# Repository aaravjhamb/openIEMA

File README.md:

<h1 align="center">OpenIEMA</h1>
<div align="center">

**OpenIEMA** is an Open Source, In Ear Monitor Amplifier built as an alternative to the Behringer P2 with dual headphone outputs driven from a mono balanced XLR input, with onboard LiPo power and USB-C charging!!

</div>

## Key Features

| | |
|---|---|
| **True balanced input** | Neutrik XLR into an OPA1678 differential line receiver which ensures any long cable runs from the mixer stay noise free |
| **Dual 3.5mm outputs** | supports up to two IEM users off one beltpack, driven by a TI TPA6132A2 DirectPath amp! |
| **Analog soft limiter** | anti parallel LEDs act as soft limiters that clamp excess noise before you hear it! |
| **Fully portable** | Uses a 1S LiPo with USB C charging (MCP73831, 500 mA) and a boost converter to a clean 5 V analog rail, charges while switched off |
| **Zero firmware** | 100% analog signal path built for simplicity |
| **3D-printed enclosure** | Includes a 3D printed enclosure with volume control all in a compact package! |

## PCB

40 × 70 mm, 2-layer, designed in KiCad 10.

**Schematic:**

**Layout:**

**3D View:**

## Case

Designed in Fusion 360

## Credits

This project uses:

- [KiCad 10](https://www.kicad.org/) for schematic capture and layout
- [pcb2blender](https://github.com/30350n/pcb2blender) for the Blender renders
- TI TPA6132A2 + OPA1678, Microchip MCP73831, TI TPS61023

## License

MIT

---

> [aaravj.tech]() · GitHub [@aaravjhamb](https://github.com/aaravjhamb/)

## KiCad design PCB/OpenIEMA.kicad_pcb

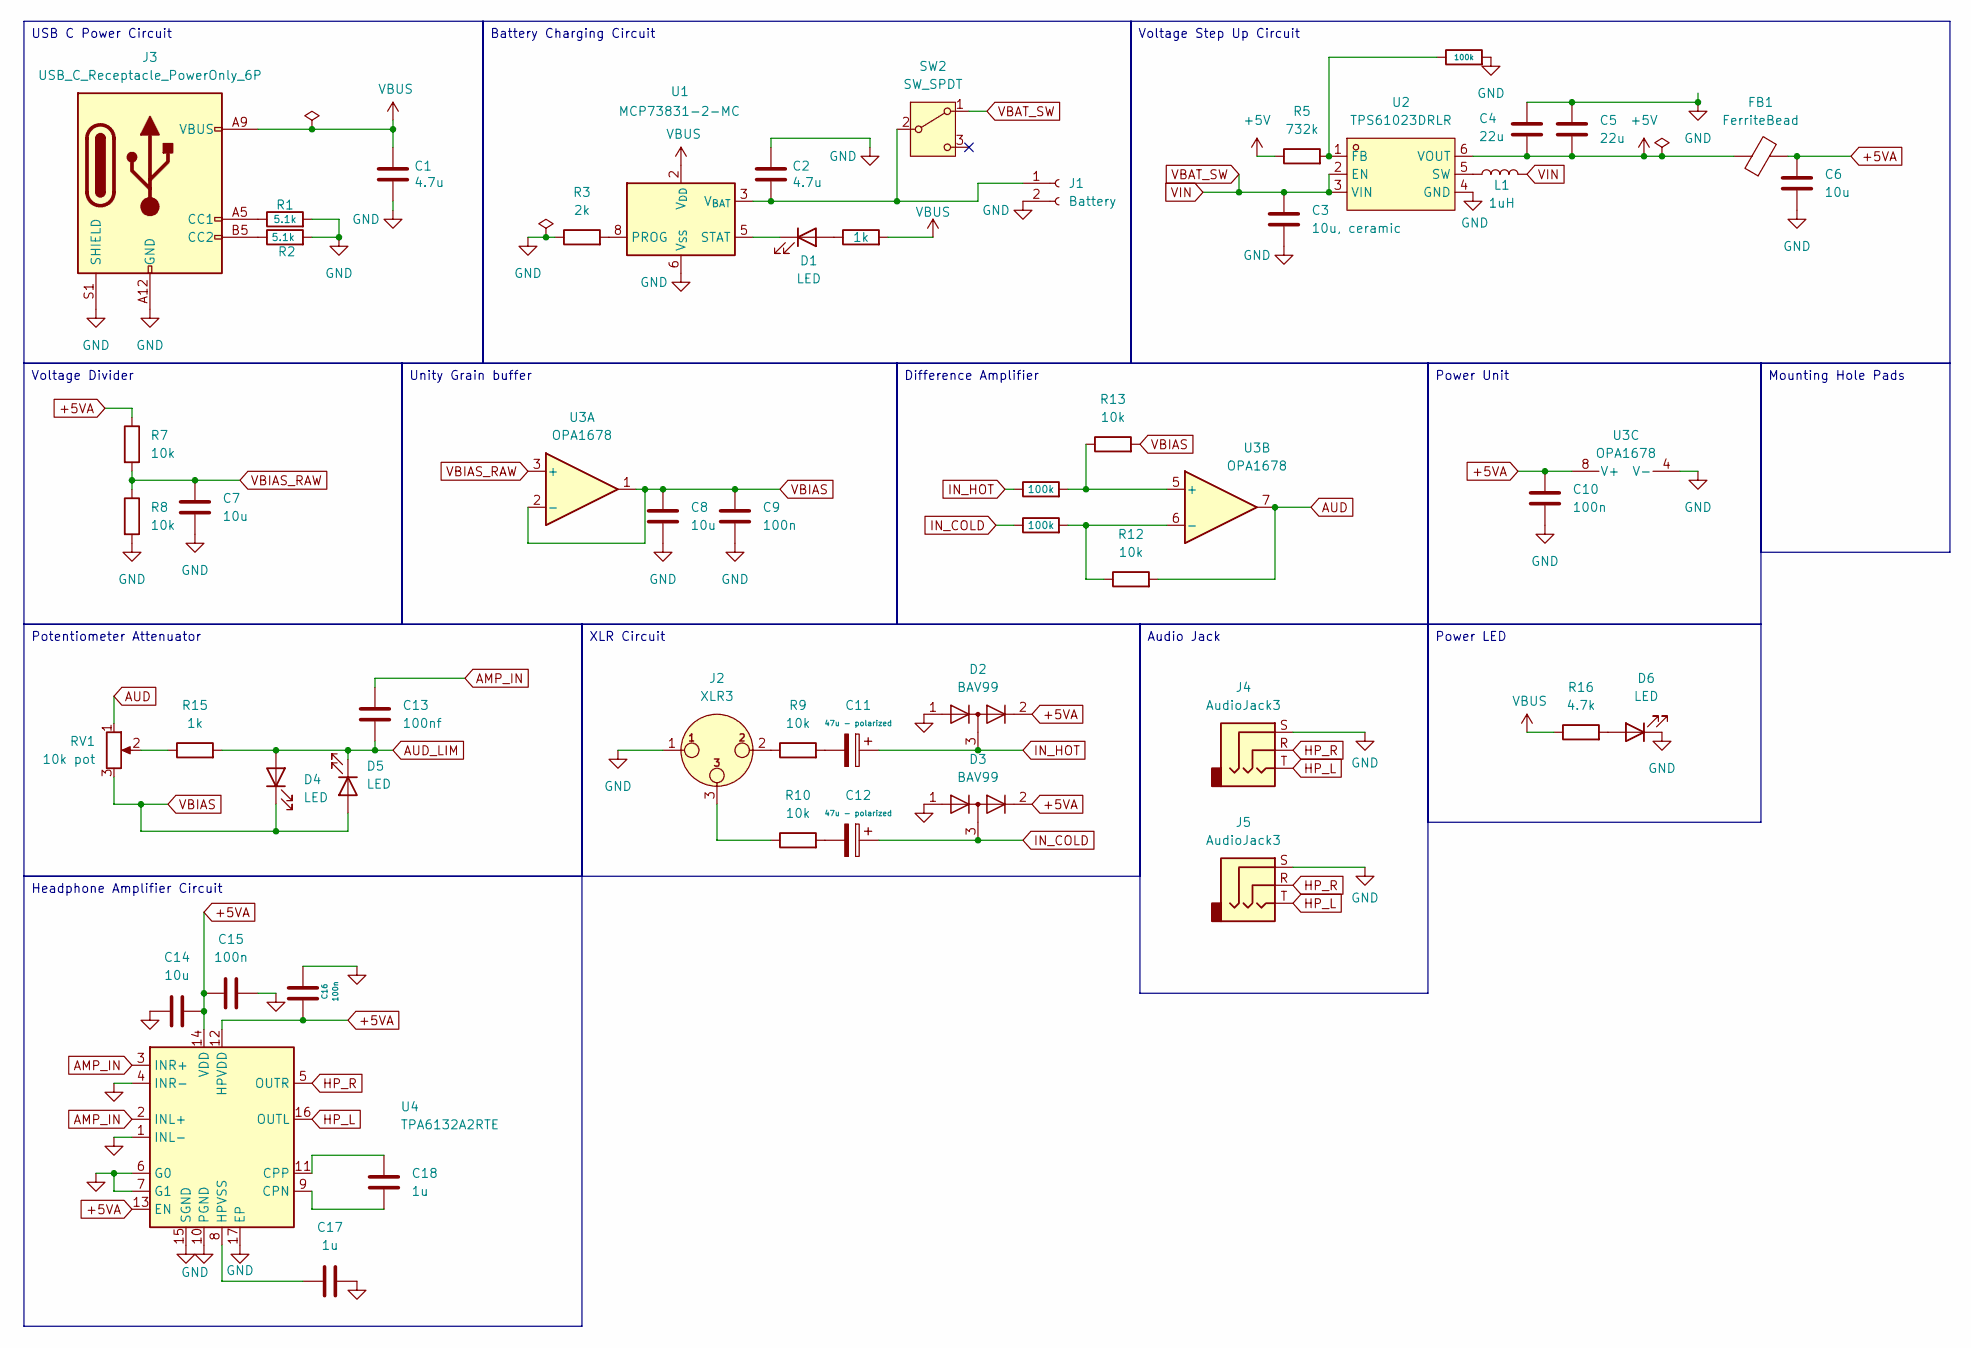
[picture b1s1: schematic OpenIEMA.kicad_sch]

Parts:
C1, C2: 4.7u; C_0402_1005Metric
C3: 10u, ceramic; C_0402_1005Metric
C4, C5: 22u; C_0402_1005Metric
C6, C7, C8, C14: 10u; C_0402_1005Metric
C9, C10, C15, C16: 100n; C_0402_1005Metric
C11, C12: 47u - polarized; CP_Elec_6.3x7.7
C13: 100nf; C_0402_1005Metric
C17, C18: 1u; C_0402_1005Metric
D1, D4, D5, D6: LED; LED_0402_1005Metric
D2, D3: BAV99; SOT-23
FB1: FerriteBead; R_0805_2012Metric
J1: Battery; JST_PH_B2B-PH-K_1x02_P2.00mm_Vertical
J2: XLR3; Jack_XLR_Neutrik_NC3FD-H_Horizontal
J3: USB_C_Receptacle_PowerOnly_6P; USB_C_Receptacle_HRO_TYPE-C-31-M-17
J4, J5: AudioJack3; Jack_3.5mm_PJ320A_Horizontal
L1: 1uH; L_Taiyo-Yuden_NR-40xx
R1, R2: 5.1k; R_0402_1005Metric
R3: 2k; R_0402_1005Metric
R4, R15: 1k; R_0402_1005Metric
R5: 732k; R_0402_1005Metric
R6, R11, R14: 100k; R_0402_1005Metric
R7, R8, R9, R10, R12, R13: 10k; R_0402_1005Metric
R16: 4.7k; R_0402_1005Metric
RV1: 10k pot; Potentiometer_Piher_PT-6-V_Vertical
SW2: SW_SPDT; SW_SPDT_PCM12
U1: MCP73831-2-MC; DFN-8-1EP_3x2mm_P0.5mm_EP1.7x1.4mm
U2: TPS61023DRLR; SOT-563_L1.6-W1.2-P0.50-LS1.6-BR; MPN TPS61023DRLR; LCSC Part C919459
U3: OPA1678; SOIC-8_3.9x4.9mm_P1.27mm
U4: TPA6132A2RTE; WQFN-16-1EP_3x3mm_P0.5mm_EP1.6x1.6mm_ThermalVias

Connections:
+5V: C4.2, C5.2, FB1.1, R5.1, U2.6 (VOUT)
+5VA: C6.1, C10.2, C14.2, C15.1, C16.1, D2.2 (A), D3.2 (A), FB1.2, R7.1, U3.8 (V+), U4.12 (HPVDD), U4.13 (EN), U4.14 (VDD)
AMP_IN: C13.1, U4.2 (INL+), U4.3 (INR+)
AUD: R12.2, RV1.1, U3.7
AUD_LIM: C13.2, D4.2 (A), D5.1 (K), R15.2
GND: C1.2, C2.1, C3.2, C4.1, C5.1, C6.2, C7.2, C8.1, C9.1, C10.1, C14.1, C15.2, C16.2, C17.1, D2.1 (K), D3.1 (K), D6.1 (K), J1.2, J2.1, J3.A12 (GND), J3.B12 (GND), J3.S1 (SHIELD), J4.S, J5.S, R1.2, R2.2, R3.1, R6.2, R8.2, U1.6 (V_{SS}), U2.4 (GND), U3.4 (V-), U4.1 (INL-), U4.4 (INR-), U4.6 (G0), U4.7 (G1), U4.10 (PGND), U4.15 (SGND), U4.17 (EP)
HP_L: J4.T, J5.T, U4.16 (OUTL)
HP_R: J4.R, J5.R, U4.5 (OUTR)
IN_COLD: C12.1, D3.3 (K), R11.1
IN_HOT: C11.1, D2.3 (K), R14.1
unnamed: C11.2, R9.2
unnamed: C12.2, R10.2
unnamed: D1.2 (A), R4.1
unnamed: D1.1 (K), U1.5 (STAT)
unnamed: D6.2 (A), R16.2
unnamed: C2.2, J1.1, SW2.2 (B), U1.3 (V_{BAT}), U1.4 (V_{BAT})
unnamed: J2.2, R9.1
unnamed: J2.3, R10.1
unnamed: J3.A5 (CC1), R1.1
unnamed: J3.B5 (CC2), R2.1
unnamed: R15.1, RV1.2
unnamed: R3.2, U1.8 (PROG)
unnamed: R5.2, R6.1, U2.1 (FB)
unnamed: L1.1, U2.5 (SW)
unnamed: R13.1, R14.2, U3.5 (+)
unnamed: R11.2, R12.1, U3.6 (-)
unnamed: C18.2, U4.9 (CPN)
unnamed: C18.1, U4.11 (CPP)
unnamed: C17.2, U4.8 (HPVSS)
VBAT_SW: C3.1, L1.2, SW2.1 (A), U2.2 (EN), U2.3 (VIN)
VBIAS: C8.2, C9.2, D4.1 (K), D5.2 (A), R13.2, RV1.3, U3.1, U3.2 (-)
VBIAS_RAW: C7.1, R7.2, R8.1, U3.3 (+)
VBUS: C1.1, J3.A9 (VBUS), J3.B9 (VBUS), R4.2, R16.1, U1.1 (V_{DD}), U1.2 (V_{DD})

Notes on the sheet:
Potentiometer Attenuator
Mounting Hole Pads
Voltage Step Up Circuit
Voltage Divider
Battery Charging Circuit
Audio Jack
Headphone Amplifier Circuit
Power LED
USB C Power Circuit
Power Unit
Difference Amplifier
Unity Grain buffer
XLR Circuit

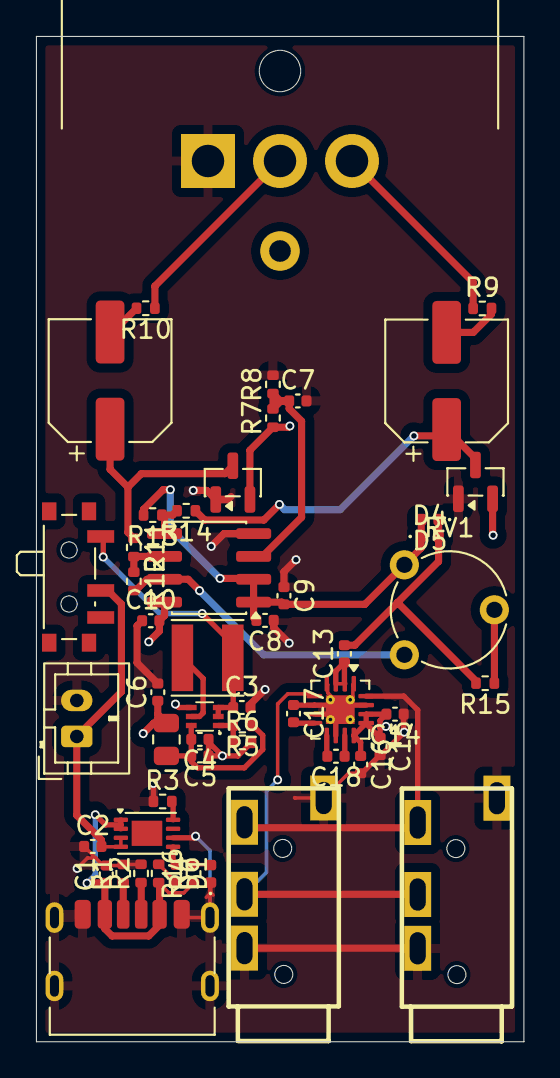
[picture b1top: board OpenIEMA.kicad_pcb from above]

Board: 4 copper layers, 27.1 x 55.9 mm, 53 parts (0 on the bottom side), 33 nets.

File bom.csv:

Designator,Qty,Value / Part,Description,Footprint / Package,LCSC Part #,Source,Cost (AUD)
"C1, C2",2,4.7u,,0603,,JLCPCB,
"C10, C15, C16, C9",4,100n,,0603,,JLCPCB,
"C11, C12",2,47u - polarized,,CP_Elec_6.3x7.7,,JLCPCB,
C13,1,100nf,,0603,,JLCPCB,
"C14, C6, C7, C8",4,10u,,0805,,JLCPCB,
"C17, C18",2,1u,,0603,,JLCPCB,
C3,1,"10u, ceramic",,0805,,JLCPCB,
"C4, C5",2,22u,,0805,,JLCPCB,
"D1, D4, D5, D6",4,LED,,0805,,JLCPCB,
"D2, D3",2,BAV99,,SOT-23,,JLCPCB,
FB1,1,FerriteBead,,0805,,JLCPCB,
J1,1,Battery,,JST_PH_B2B-PH-K_1x02_P2.00mm_Vertical,,JLCPCB,
J2,1,XLR3,,Jack_XLR_Neutrik_NC3FD-H_Horizontal,,JLCPCB,
J3,1,USB_C_Receptacle_PowerOnly_6P,,USB_C_Receptacle_HRO_TYPE-C-31-M-17,,JLCPCB,
"J4, J5",2,AudioJack3,,Jack_3.5mm_PJ320A_Horizontal,C12569,JLCPCB,
L1,1,1uH,,L_Taiyo-Yuden_NR-40xx,,JLCPCB,
"R1, R2",2,5.1k,,0603,,JLCPCB,
"R10, R12, R13, R7, R8, R9",6,10k,,0603,,JLCPCB,
"R11, R14, R6",3,100k,,0603,,JLCPCB,
"R15, R4",2,1k,,0603,,JLCPCB,
R16,1,4.7k,,0603,,JLCPCB,
R3,1,2k,,0603,,JLCPCB,
R5,1,732k,,0603,,JLCPCB,
RV1,1,10k pot,,Potentiometer_Bourns_PTV09A_Single_Vertical,,JLCPCB,
SW2,1,SW_SPDT,,SW_SPDT_PCM12,,JLCPCB,
"TP1, TP2, TP3, TP4, TP5, TP6",6,TestPoint,,TestPoint_Pad_D1.5mm,,JLCPCB,
U1,1,MCP73831-2-MC,,DFN-8-1EP_3x2mm_P0.5mm_EP1.7x1.4mm,,JLCPCB,
U2,1,TPS61023DRLR,,SOT-563_L1.6-W1.2-P0.50-LS1.6-BR,C919459,JLCPCB,
U3,1,OPA1678,,SOIC-8_3.9x4.9mm_P1.27mm,,JLCPCB,
U4,1,TPA6132A2RTE,,WQFN-16-1EP_3x3mm_P0.5mm_EP1.6x1.6mm_ThermalVias,,JLCPCB,
,1,Silk PLA,Case,,,Jaycar,$19
,1,IEM,In ear monitors for testing,,,https://www.amazon.com.au/KS1-Headphones-Resolution-Detachab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,$25
,1,Polymer Lithium Ion Battery (LiPo) 3.7V 1100mAh,Battery,,,https://core-electronics.com.au/polymer-lithium-ion-battery-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,$9
,,,,,,Non-PCB subtotal,$53
